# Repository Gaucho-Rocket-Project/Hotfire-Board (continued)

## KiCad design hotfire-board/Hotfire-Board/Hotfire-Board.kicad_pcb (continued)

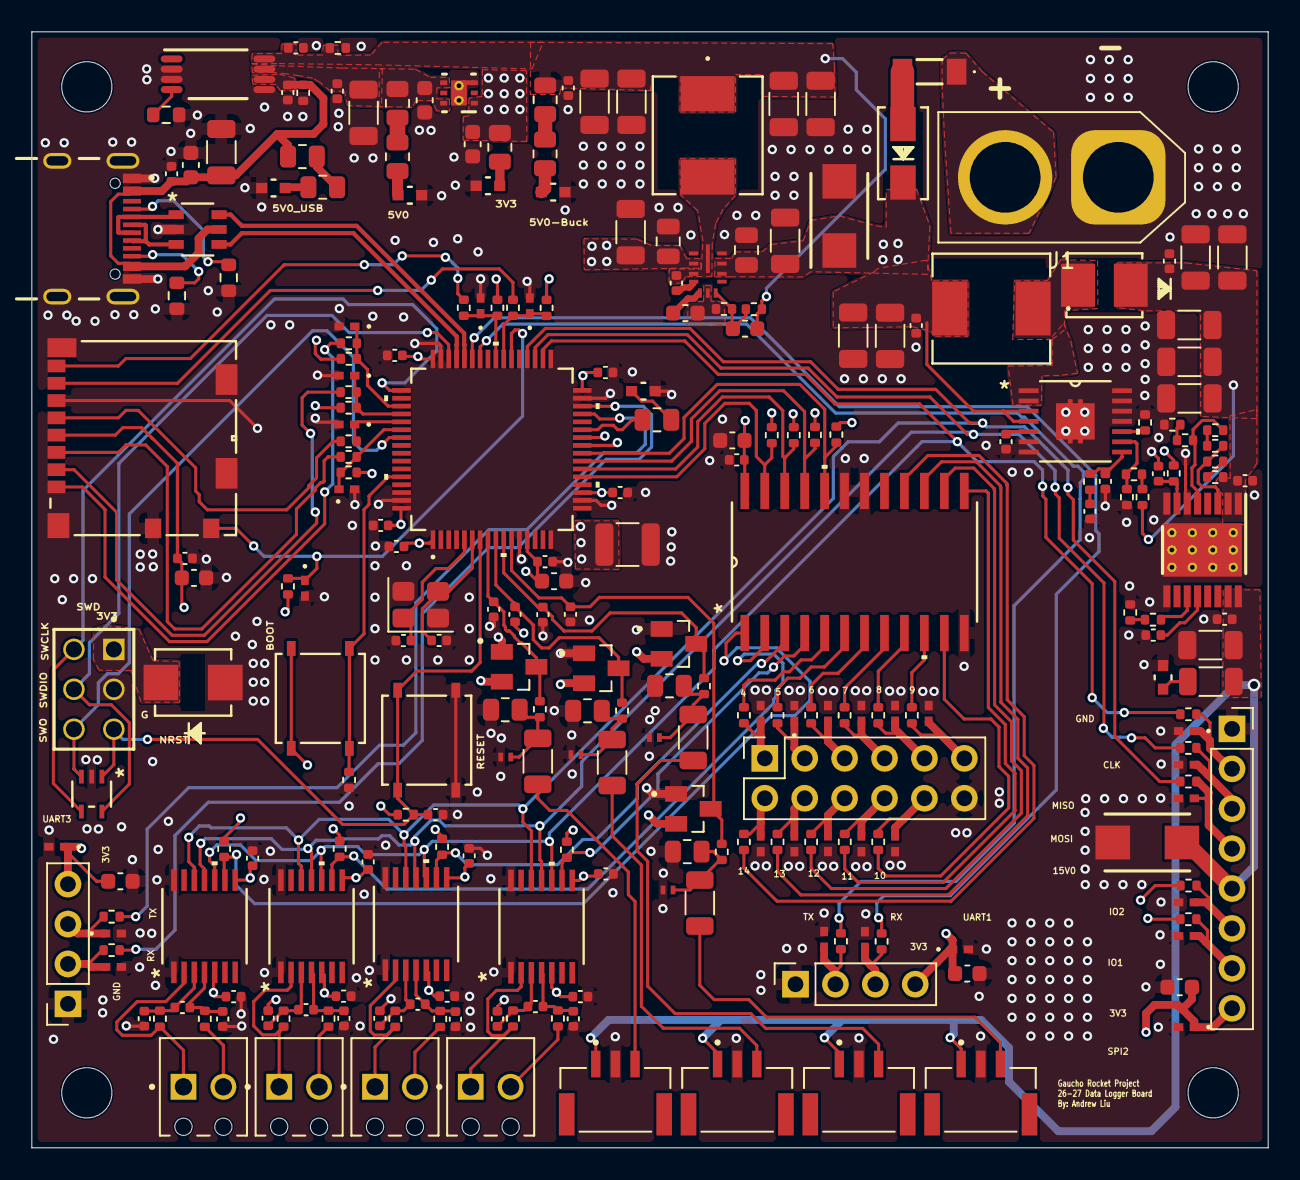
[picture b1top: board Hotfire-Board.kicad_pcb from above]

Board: 4 copper layers, 78.7 x 71.0 mm, 260 parts (0 on the bottom side), 143 nets.

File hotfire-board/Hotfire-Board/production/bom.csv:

Designator,Footprint,Quantity,Value,LCSC Part #
"C1, C15, C18, C21, C26, C29, C30, C31, C36, C37, C38, C41, C42, C44, C45, C46, C47, C48, C49, C50, C51, C52, C53, C54, C55, C60, C61, C66, C67, C68, C74, C75, C76, C78, C79, C9",0402,36,0.1u,
"C10, C40, C56, C57, C58, C59, C62, C63, C64, C65",0402,10,10n,
"C11, C2, C20, C22, C24, C3, C5, C6, C72, C73, C77",1206,11,4.7u,
"C12, C14, C17, C39, C4, C43, C69, C70, C71, C80",0603,10,1u,
C13,0402,1,270n,
C16,0402,1,100p,
C19,0603,1,CFF,
"C23, C25, C27, C28, C32",1206,5,22u,
"C33, C34",0402,2,10p,
C35,1210,1,10u,
"C7, C8",0805,2,220n,
CR1,Shottkey_Rev_Bat,1,B1100-13-F,
CR3,ESDPROTECTION,1,USBLC6-2SC6,USBLC6-2SC6 
CR4,SWD_1_TVS,1,SMLVT3V3,
CR5,SWD_4_TVS,1,ESDALC6V1W5,
"CR6, CR7, CR8, CR9",TVS_Input,4,SP1233-01ETG,
"D1, D12, D13, D14, D15, D16, D17, D18, D19, D2, D20, D21, D22, D23, D26, D27, D28, D29, D3, D30, D31, D32, D33, D34, D35, D36, D4, D5, D8, D9",SD_ESD,30,TPD1E05U06DPYR,
"D10, D11, D6, D7",dual_shottkey,4,BAT54S,
D24,15V_TVS,1,SMBJ15A,
D25,18V_TVS,1,SMBJ18A,
F1,fuse,1,SF-1206S100-2,
J1,AMASS_XT60-M_1x02_P7.20mm_Vertical,1,Conn_01x02,
"J10, J5, J7, J9",3-pin-jst,4,SM03B-GHS-TB,
"J11, J12, J13, J14",screw_terminal,4,1725656,
J15,PinSocket_1x08_P2.54mm_Vertical,1,Conn_01x08,
J16,PinSocket_2x06_P2.54mm_Vertical,1,C36191,
J2,3x2_Header,1,BCS-103-L-D-TE,
J3,PinSocket_1x04_P2.54mm_Vertical,1,UART1,
J4,PinSocket_1x04_P2.54mm_Vertical,1,UART3,
J6,USB,1,USB4105-GF-A-060,USB4105-GF-A-060 
J8,SD_Card,1,MEM2061-01-188-00-A_REVA,
"L1, L2",22uH,2,IHLP2525CZER220M5A,
"LED1, LED2, LED3, LED4, LED5, LED6",red_LED,6,LTST-C190KRKT,
"R1, R14, R15, R28, R29, R35, R42, R61, R71, R79, R91, R92",0805,12,130,
"R10, R11, R6, R65, R66, R74",0402,6,100k,
"R12, R37, R38, R39, R40, R63, R69, R72, R75, R76, R77, R78, R9",0402,13,10k,
R13,0603,1,400,PAT0603E4000BST1
"R16, R17, R18, R19, R20, R21",0402,6,22,
"R2, R68",0402,2,590,
"R22, R23, R24, R27, R32, R33",0402,6,47k,
"R25, R26, R34, R41",1206,4,20,
"R3, R4",0603,2,5.1k,0603WAF5101T5E
"R30, R31, R36, R43, R67, R70, R73",0402,7,4.7k,
"R44, R45, R46, R47, R48, R49, R50, R51, R52, R53, R54, R55, R56, R57, R58, R59, R60, R80, R81, R82, R83, R84, R85, R86, R87, R88, R89, R90",0402,28,100,
R5,0402,1,43.2k,
"R62, R64",0402,2,68.1k,
R7,0402,1,24.9k,
R8,1206,1,1.3k,
SW1,SWITCH,1,RESET,
SW2,SWITCH,1,BOOT,
U1,3.3V_Buck,1,LMR36006BRNXR,
U10,Boost_Shottkey,1,SS34,
U11,4-16-Multiplexer,1,CD74HC154M96,
U12,eFuse,1,TPS26600PWPR,
U2,15V_Boost,1,TPS55340PWPR,
U3,STM32,1,STM32L496RET6,
U4,PowerMUXER.,1,TPS2113APW,
U5,LDO,1,LP5912-3.3DRVR,LP5912-3.3DRVR 
"U6, U7, U8, U9",MAX,4,MAX31856MUD+,
Y1,Crystal_SMD_3225-4Pin_3.2x2.5mm,1,16MHz,

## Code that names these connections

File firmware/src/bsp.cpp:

#include "bsp.hpp"

#include <zephyr/devicetree.h>
#include <zephyr/device.h>
#include <zephyr/drivers/adc.h>
#include <zephyr/drivers/gpio.h>
#include <zephyr/drivers/spi.h>
#include <zephyr/sys/util.h>

namespace bsp {

const gpio_dt_spec user_led = GPIO_DT_SPEC_GET(DT_ALIAS(led0), gpios);
const device* const uart1 = DEVICE_DT_GET(DT_ALIAS(telemetry_uart));
const device* const rtc = DEVICE_DT_GET(DT_NODELABEL(rtc));
const device* const entropy = DEVICE_DT_GET(DT_CHOSEN(zephyr_entropy));
const gpio_dt_spec sd_card_detect = GPIO_DT_SPEC_GET(DT_NODELABEL(sdmmc1), cd_gpios);

const device* const sensor_spi = DEVICE_DT_GET(DT_NODELABEL(spi2));
// MAX31856: 1 MHz, mode 3, 8-bit MSB first. The CD74HC154 controls CS.
// Both sensors support mode 3; keep SCK polarity consistent on the shared bus.
const spi_config thermocouple_spi_config = [] {
    spi_config config{};
    config.frequency = 1000000;
    config.operation = SPI_OP_MODE_CONTROLLER | SPI_WORD_SET(8) |
                       SPI_TRANSFER_MSB | SPI_MODE_CPOL | SPI_MODE_CPHA;
    config.peripheral = 0;
    return config;
}();

// ADXL345: same bus, 1 MHz requested, mode 3. Decoder output Y13 is board net CS13.
const spi_config accelerometer_spi_config = [] {
    spi_config config{};
    config.frequency = 1000000;
    config.operation = SPI_OP_MODE_CONTROLLER | SPI_WORD_SET(8) |
                       SPI_TRANSFER_MSB | SPI_MODE_CPOL | SPI_MODE_CPHA;
    config.peripheral = 0;
    return config;
}();
const uint8_t thermocouple_decoder_addresses[4] = {0, 1, 2, 3};
const uint8_t accelerometer_decoder_address = 13;

// A0-A2: PA5-PA7. A3: PC4. Y4-Y7 and Y15 are reserved for parking; address 15 is idle.
const DecoderAddressPort spi_decoder_low = {
    DEVICE_DT_GET(DT_NODELABEL(gpioa)), 5, 3, BIT(5) | BIT(6) | BIT(7)
};
const gpio_dt_spec spi_decoder_a3 = {
    DEVICE_DT_GET(DT_NODELABEL(gpioc)), 4, GPIO_ACTIVE_HIGH
};

constexpr adc_dt_spec pressure_inputs[pressure_channel_count] = {
    ADC_DT_SPEC_GET_BY_IDX(DT_PATH(zephyr_user), 0),
    ADC_DT_SPEC_GET_BY_IDX(DT_PATH(zephyr_user), 1),
    ADC_DT_SPEC_GET_BY_IDX(DT_PATH(zephyr_user), 2),
    ADC_DT_SPEC_GET_BY_IDX(DT_PATH(zephyr_user), 3),
};
static_assert(pressure_inputs[0].channel_id == 1 && pressure_inputs[1].channel_id == 2 &&
              pressure_inputs[2].channel_id == 3 && pressure_inputs[3].channel_id == 4,
              "Pressure scan packing assumes ADC channels 1..4 in ascending order");
const char* const pressure_channel_labels[pressure_channel_count] = {
    "J5, PC0 / ADC1 IN1", "J9, PC1 / ADC1 IN2",
    "J10, PC2 / ADC1 IN3", "J7, PC3 / ADC1 IN4"
};

const ExpansionGpio expansion_gpios[expansion_gpio_count] = {
    {DEVICE_DT_GET(DT_NODELABEL(gpiob)), 0, "0", "PB0", 6},
    {DEVICE_DT_GET(DT_NODELABEL(gpioc)), 5, "1", "PC5", 7},
};

const size_t ram_bytes = DT_REG_SIZE(DT_CHOSEN(zephyr_sram));
const size_t flash_bytes = DT_REG_SIZE(DT_CHOSEN(zephyr_flash));

} // namespace bsp
